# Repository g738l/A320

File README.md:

# A320
Simulation LED Anti-Collision Lighting System for Airbus A320 Family

## License
This project is released under the Creative Commons Attribution-NonCommercial-ShareAlike 3.0 (CC-BY-NC-SA 3.0, https://creativecommons.org/licenses/by-nc-sa/3.0/) license. You may edit and share it as you like, as long as credit is given and the license is not changed. You can build as many boards for you and your friends as you like and you can even sell it to them to cover your costs, **however it is strictly forbidden to turn this into a commercial product! You are not allowed to build and sell these boards for profit!**

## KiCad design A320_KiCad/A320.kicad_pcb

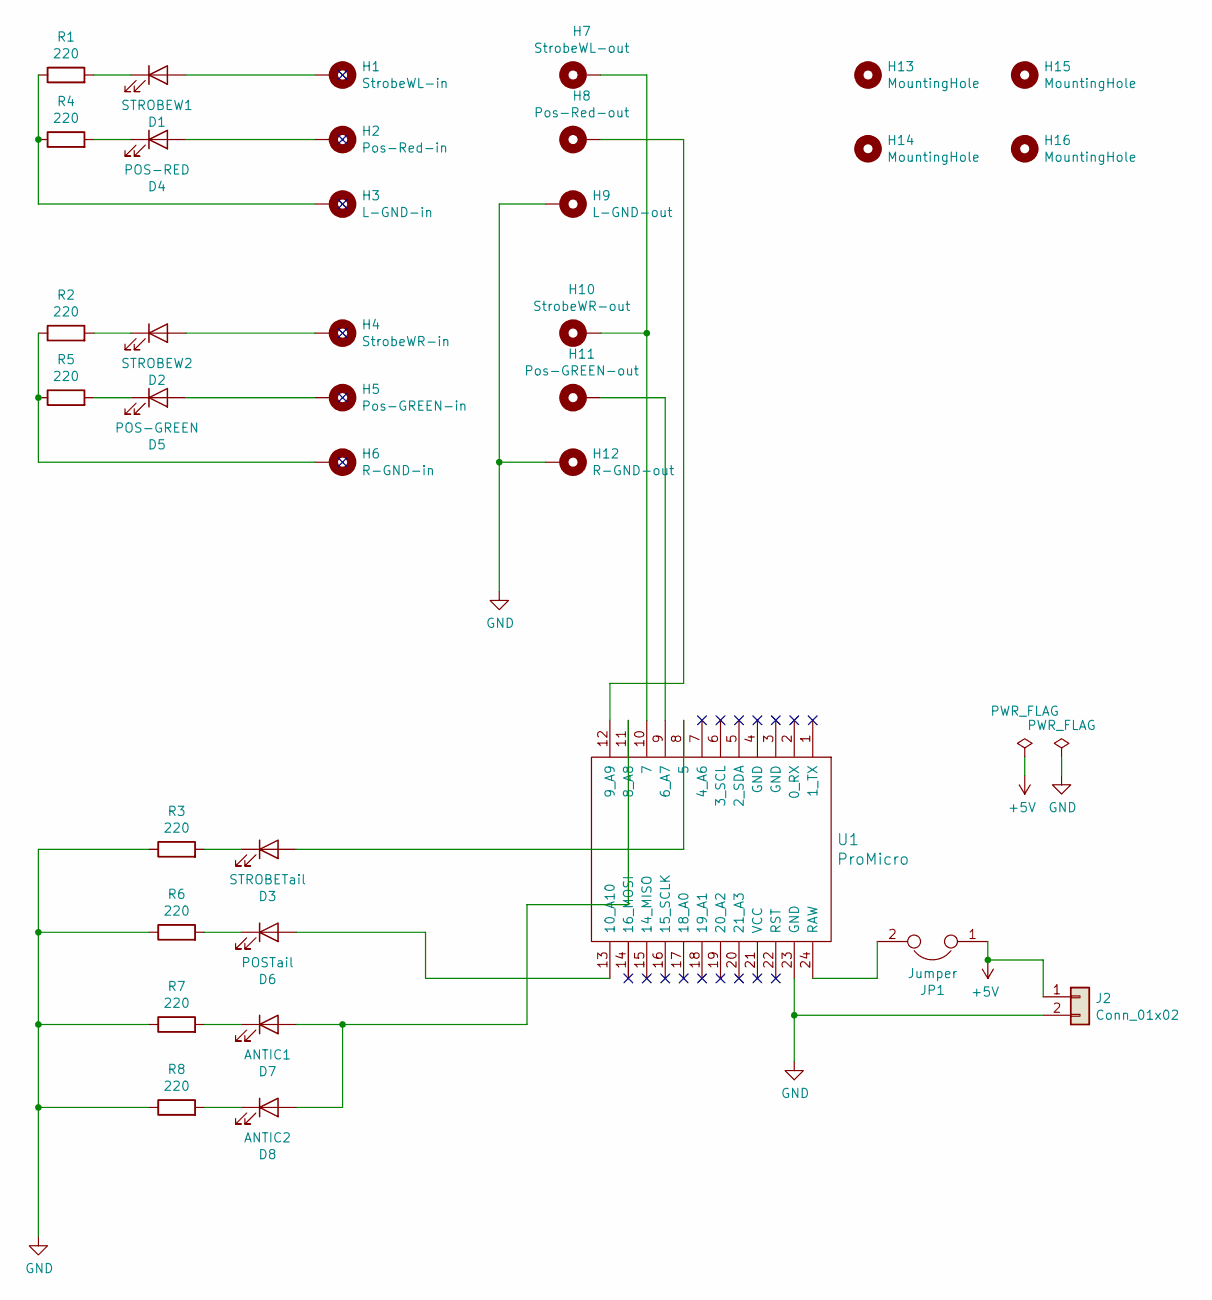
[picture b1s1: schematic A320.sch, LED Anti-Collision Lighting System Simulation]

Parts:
D1: STROBEW1; LED_D3.0mm_Horizontal_O3.81mm_Z2.0mm
D2: STROBEW2; LED_D3.0mm_Horizontal_O3.81mm_Z2.0mm
D3: STROBETail; LED_D3.0mm_Horizontal_O1.27mm_Z2.0mm
D4: POS-RED; LED_D3.0mm_Horizontal_O1.27mm_Z2.0mm
D5: POS-GREEN; LED_D3.0mm_Horizontal_O1.27mm_Z2.0mm
D6: POSTail; LED_D3.0mm_Horizontal_O3.81mm_Z2.0mm
D7: ANTIC1; LED_D3.0mm_FlatTop
D8: ANTIC2; LED_D3.0mm_FlatTop
H1: StrobeWL-in; SolderWirePad_single_1-2mmDrill
H2: Pos-Red-in; SolderWirePad_single_1-2mmDrill
H3: L-GND-in; SolderWirePad_single_1-2mmDrill
H4: StrobeWR-in; SolderWirePad_single_1-2mmDrill
H5: Pos-GREEN-in; SolderWirePad_single_1-2mmDrill
H6: R-GND-in; SolderWirePad_single_1-2mmDrill
H7: StrobeWL-out; SolderWirePad_single_1-2mmDrill
H8: Pos-Red-out; SolderWirePad_single_1-2mmDrill
H9: L-GND-out; SolderWirePad_single_1-2mmDrill
H10: StrobeWR-out; SolderWirePad_single_1-2mmDrill
H11: Pos-GREEN-out; SolderWirePad_single_1-2mmDrill
H12: R-GND-out; SolderWirePad_single_1-2mmDrill
H13, H14, H15, H16: MountingHole; MountingHole_2.5mm
J2: Conn_01x02; Pin_Header_Angled_1x02_Pitch2.54mm
JP1: Jumper; ON-OFF-SWITH
R1, R2, R3, R4, R5, R6, R7, R8: 220; R_0805_HandSoldering
U1: ProMicro

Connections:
+5V: J2.1, JP1.1
GND: H9.1, H12.1, J2.2, R3.1, R6.1, R7.1, R8.1, U1.23 (GND)
unnamed: D1.1 (K), R1.2
unnamed: D1.2 (A), H1.1
unnamed: D2.1 (K), R2.2
unnamed: D2.2 (A), H4.1
unnamed: D3.1 (K), R3.2
unnamed: D3.2 (A), U1.8 (5)
unnamed: D4.1 (K), R4.2
unnamed: D4.2 (A), H2.1
unnamed: D5.1 (K), R5.2
unnamed: D5.2 (A), H5.1
unnamed: D6.1 (K), R6.2
unnamed: D6.2 (A), U1.13 (10_A10)
unnamed: D7.1 (K), R7.2
unnamed: D7.2 (A), D8.2 (A), U1.11 (8_A8)
unnamed: D8.1 (K), R8.2
unnamed: H3.1, R1.1, R4.1
unnamed: H6.1, R2.1, R5.1
unnamed: H8.1, U1.12 (9_A9)
unnamed: H7.1, H10.1, U1.10 (7)
unnamed: H11.1, U1.9 (6_A7)
unnamed: JP1.2, U1.24 (RAW)

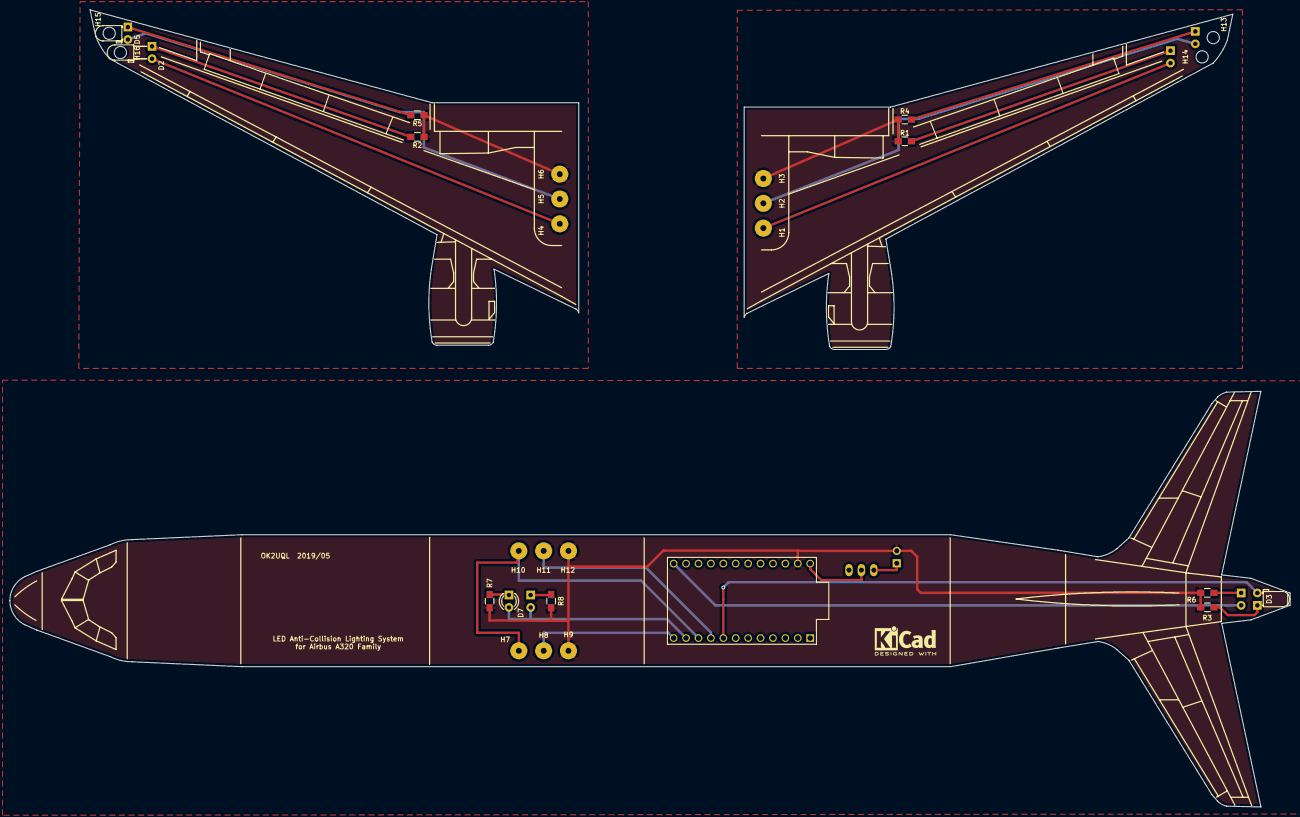
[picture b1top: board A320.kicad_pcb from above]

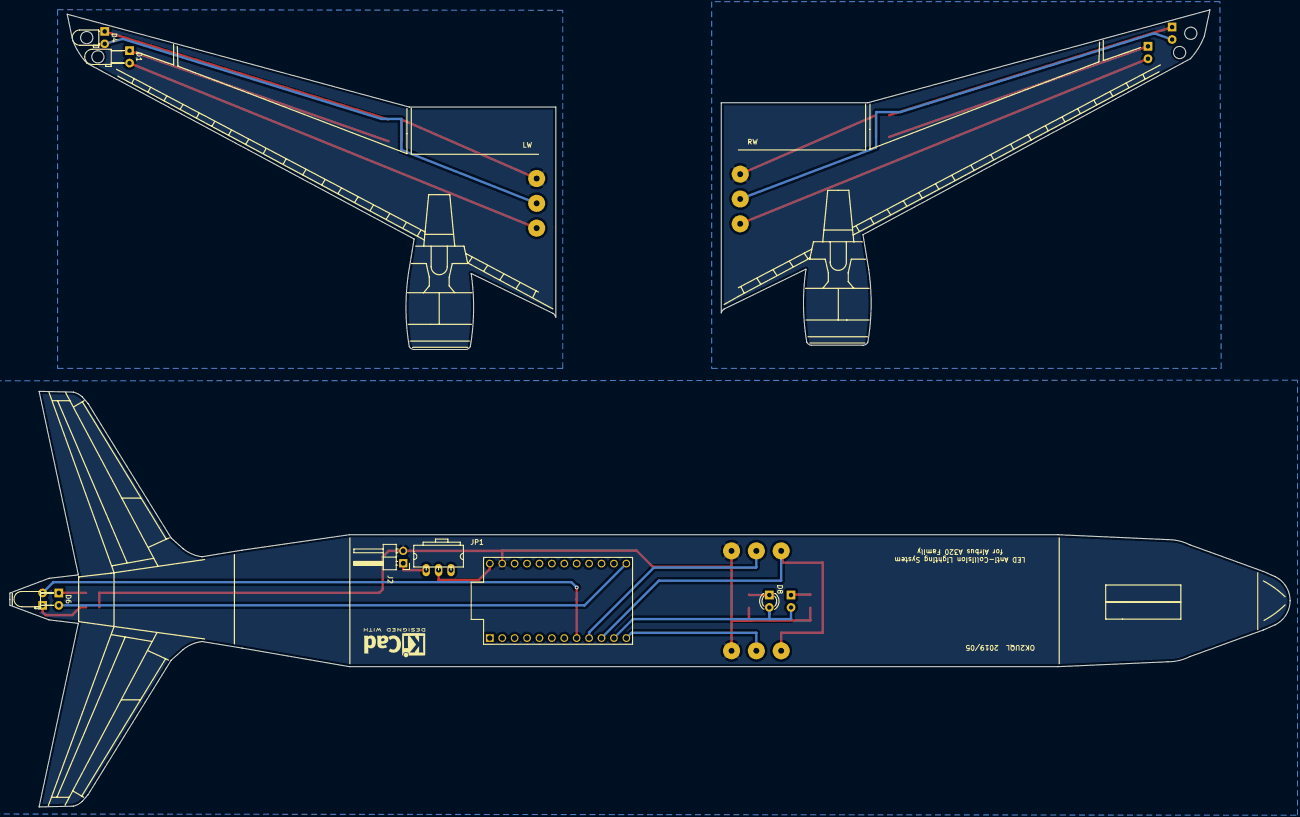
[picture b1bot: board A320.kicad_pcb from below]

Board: 2 copper layers, 262.0 x 163.1 mm, 35 parts (7 on the bottom side), 23 nets.

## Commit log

2019-10-22 Create 3Dprint
2021-03-03 Create AD
